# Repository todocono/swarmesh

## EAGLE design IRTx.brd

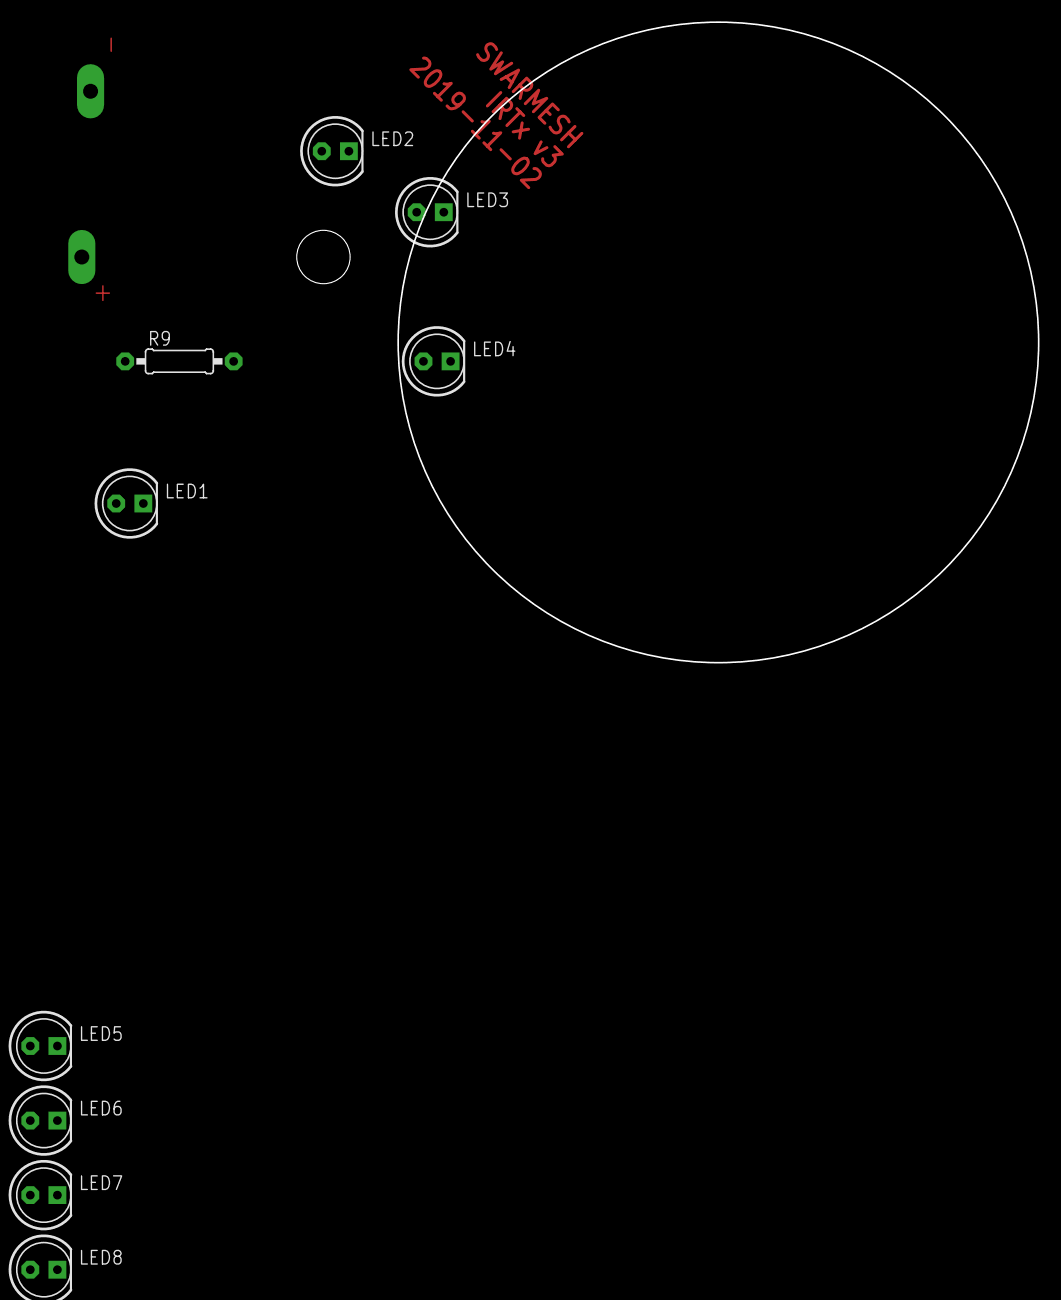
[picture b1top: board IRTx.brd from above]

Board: 2 copper layers, 60.0 x 60.0 mm, 11 parts (0 on the bottom side), 3 nets, no tracks yet.

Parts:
JP1: 3.3; 1X1-BIGPOGO
JP2: GND; 1X1-BIGPOGO
LED1, LED2, LED3, LED4, LED5, LED6, LED7, LED8: LED5MM
R9: 1k; 0207/10

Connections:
GND: JP2.P$1, LED1.K, LED2.K, LED3.K, LED4.K, LED5.K, LED6.K, LED7.K, LED8.K
unnamed: LED1.A, LED2.A, LED3.A, LED4.A, LED5.A, LED6.A, LED7.A, LED8.A, R9.1
VCC: JP1.P$1, R9.2

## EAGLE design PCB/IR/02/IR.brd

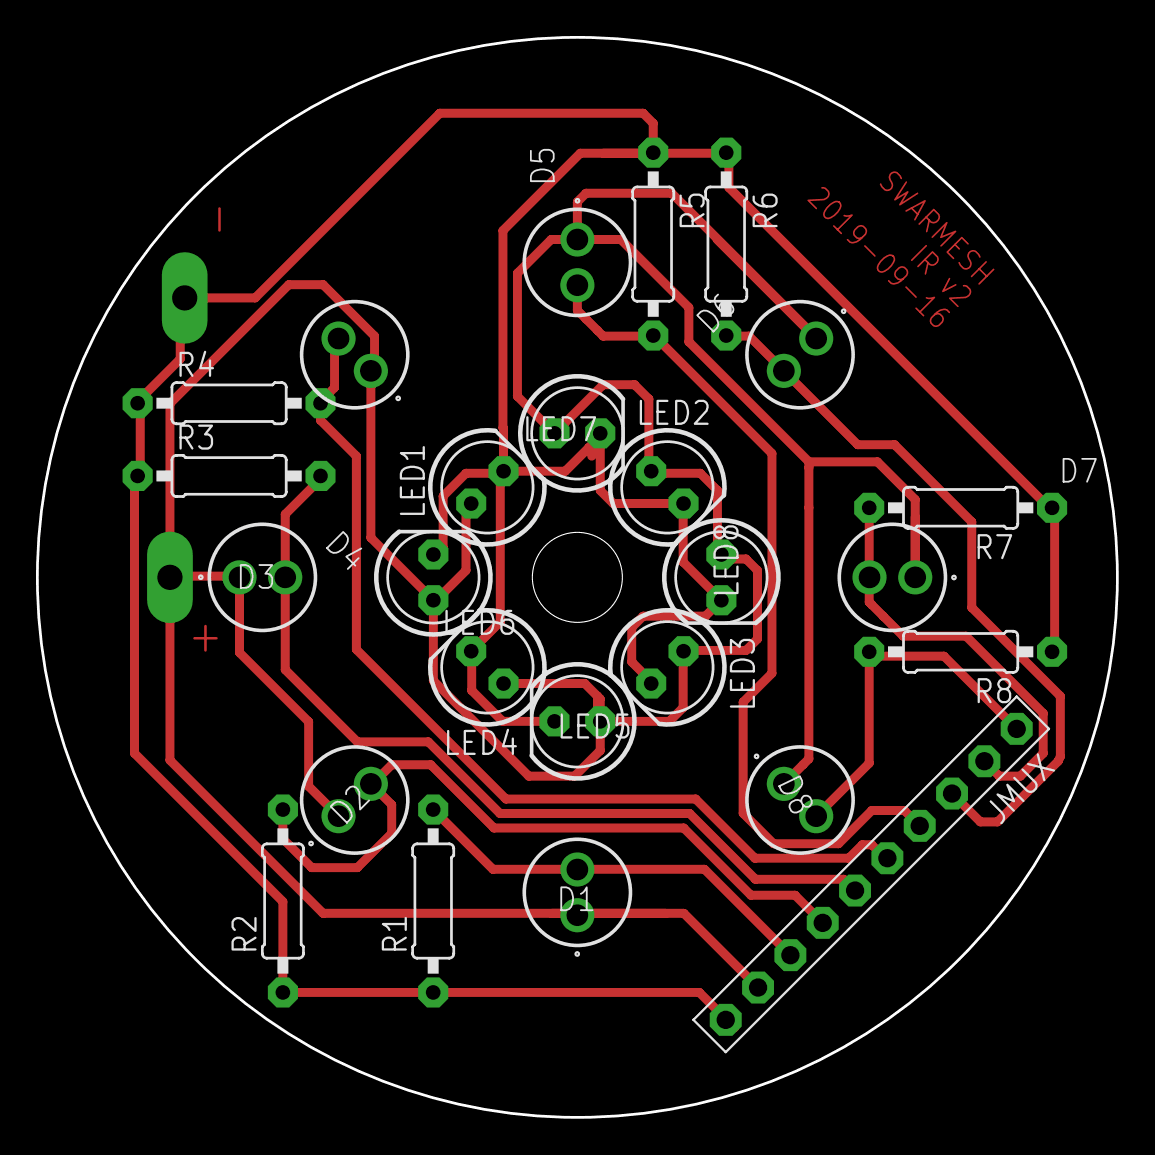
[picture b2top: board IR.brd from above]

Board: 2 copper layers, 60.0 x 60.0 mm, 27 parts (0 on the bottom side), 10 nets.

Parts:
D1, D2, D3, D4, D5, D6, D7, D8: SFH_203_PFA; SFH213_1
JMUX: PINHD-1X10; 1X10-BIG
JP9: GND; 1X1-BIGPOGO
JP10: 3.3; 1X1-BIGPOGO
LED1, LED2, LED3, LED4, LED5, LED6, LED7, LED8: LED5MM
R1, R2, R3, R4, R5, R6, R7, R8: 0207/10

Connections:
GND: JMUX.10, JP9.P$1, LED1.K, LED2.K, LED3.K, LED4.K, LED5.K, LED6.K, LED7.K, LED8.K, R1.1, R2.1, R3.1, R4.1, R5.1, R6.1, R7.1, R8.1
unnamed: D1.2, JMUX.8, R1.2
unnamed: D2.2, JMUX.7, R2.2
unnamed: D3.2, JMUX.6, R3.2
unnamed: D4.2, JMUX.5, R4.2
unnamed: D5.2, JMUX.4, R5.2
unnamed: D6.2, JMUX.3, R6.2
unnamed: D7.2, JMUX.2, R7.2
unnamed: D8.2, JMUX.1, R8.2
VCC: D1.1, D2.1, D3.1, D4.1, D5.1, D6.1, D7.1, D8.1, JMUX.9, JP10.P$1, LED1.A, LED2.A, LED3.A, LED4.A, LED5.A, LED6.A, LED7.A, LED8.A

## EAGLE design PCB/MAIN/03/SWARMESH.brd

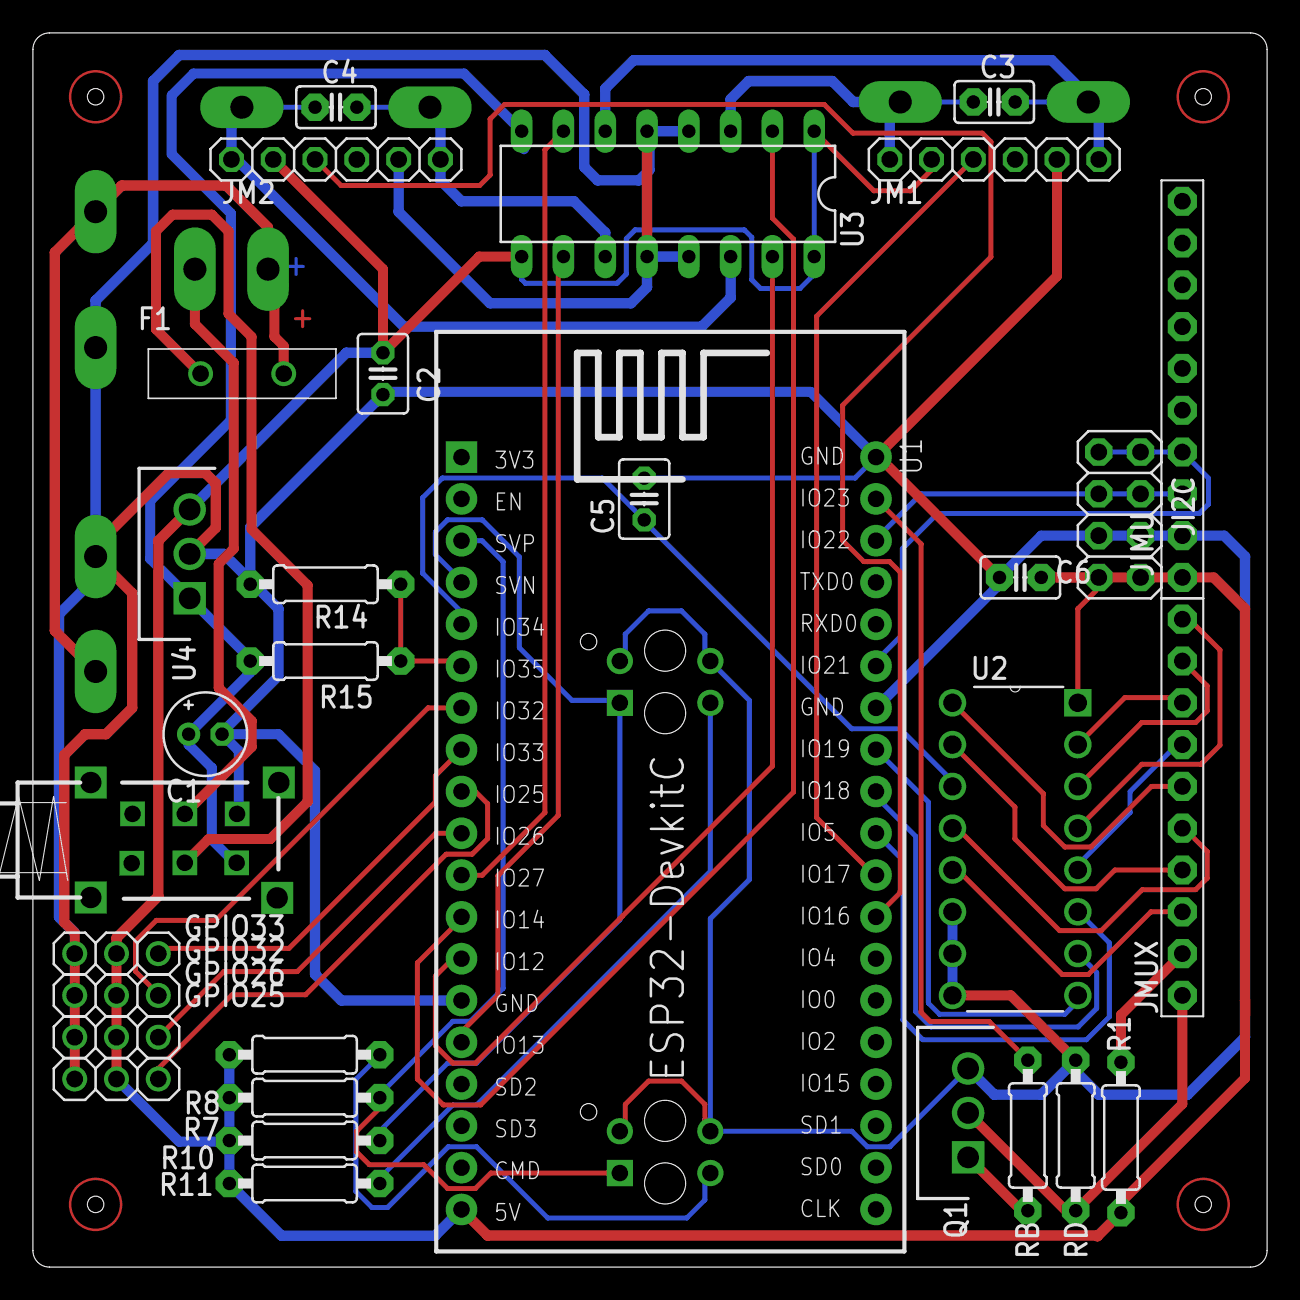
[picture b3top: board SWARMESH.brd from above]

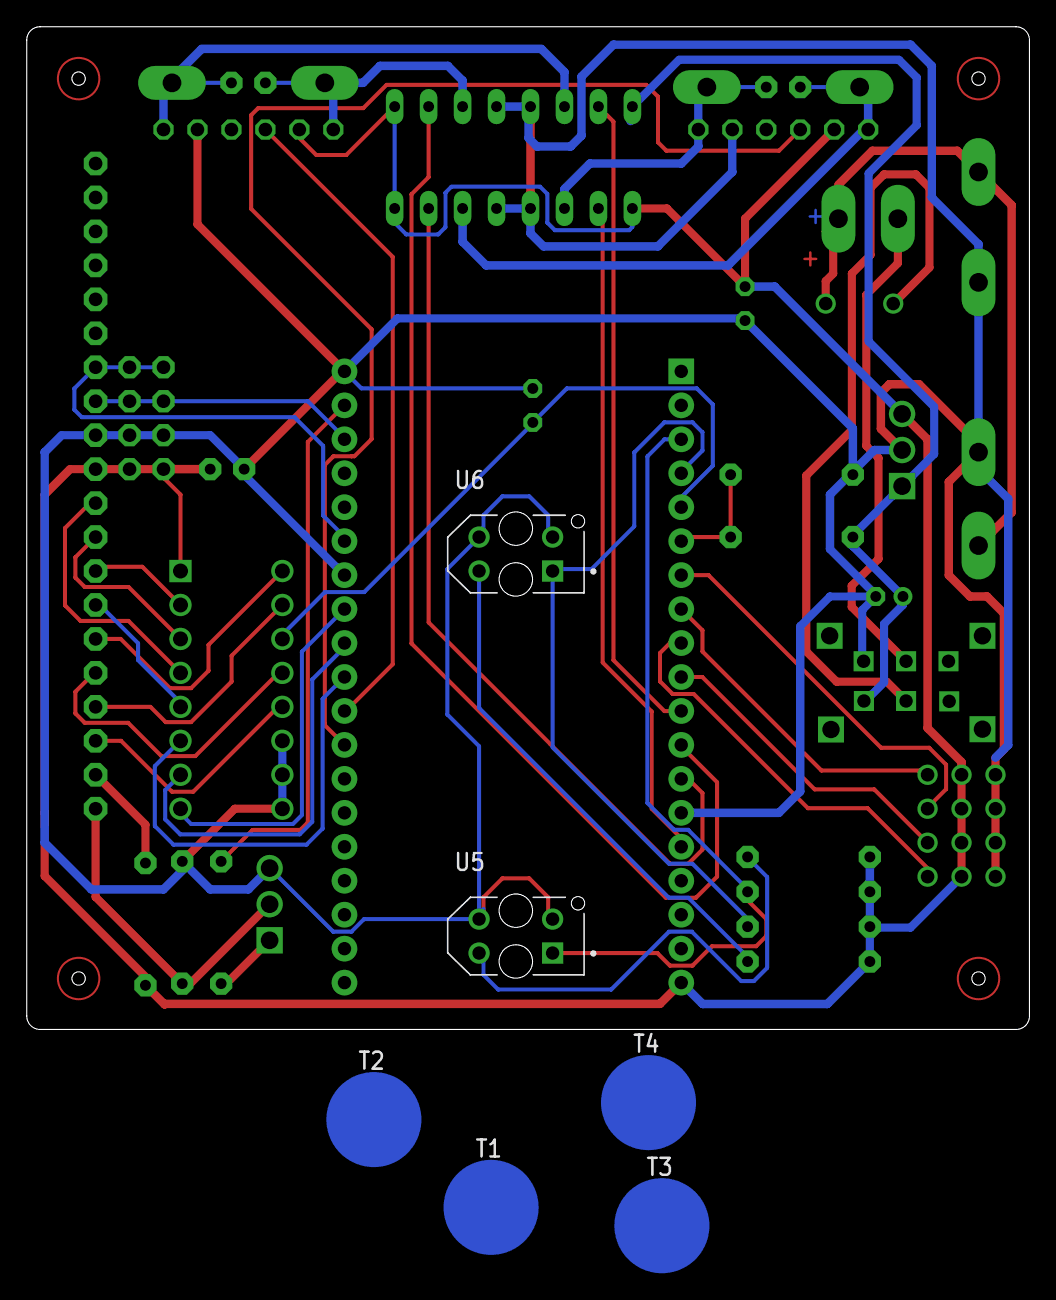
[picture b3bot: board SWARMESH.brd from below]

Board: 2 copper layers, 75.0 x 75.0 mm, 47 parts (7 on the bottom side), 47 nets.

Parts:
BAT+: 1X1-BIGPOGO
BAT-: 1X1-BIGPOGO
C1: 10uF; E2-5
C2, C5: C025-030X050
C3, C4, C6: C025-025X050
CHG1+, CHG1-, CHG2+, CHG2-: 1X1-BIGPOGO
F1: RUEF300K-2; RUEF300K2
GPIO25, GPIO26, GPIO32, GPIO33: 1X03
JI2C: 2X04
JIMU: PINHD-1X10; 1X10-BIG
JM1, JM2: 1X06
JMUX: PINHD-1X10; 1X10-BIG
JP1, JP2, JP3, JP4: 1X1-BIGPOGO
Q1: TIP122; TO270P460X1020X2008-3P
R1: 220; 0207/9
R7, R10: 1k; 0207/9
R8, R11: 100; 0207/9
R14: 10k; 0207/9
R15: 47k; 0207/9
RB: 1k; 0207/9
RD: 0; 0207/9
S1: PS22F03
T1, T2, T3, T4: SPRING-CONNECTOR
U1: ESP32DEVKITC; ESP32-DEVKITC
U2: CD4051BEE4; CD4051BEE4DIP
U3: L293D; DIL16
U4: L7805CV-DG; TO270P460X1020X2008-3P
U5, U6: TCRT5000L; XDCR_TCRT5000L

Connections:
ADCMX: C5.1, U1.5, U2.3
BATLVL: R14.2, R15.1, U1.6
E1A: JM1.3, U1.28
E2A: JM2.3, U1.27
GND: C1.-, C2.2, C5.2, C6.2, CHG1-.P$1, CHG2-.P$1, GPIO25.3, GPIO26.3, GPIO32.3, GPIO33.3, JI2C.3, JI2C.4, JIMU.2, JM1.5, JM2.5, Q1.3, R14.1, RD.2, S1.NO1, U1.14, U1.32, U1.38, U2.6, U2.7, U2.8, U3.4, U3.5, U3.12, U3.13, U4.2, U5.2, U5.3, U6.2, U6.3
IO5: U1.29, U2.11
IO12: U1.13, U3.15
IO13: U1.15, U3.10
IO14: U1.12, U3.2
IO25: GPIO25.1, U1.9
IO26: GPIO26.1, U1.10
IO27: U1.11, U3.7
IO32: GPIO32.1, U1.7
IO33: GPIO33.1, U1.8
IR1: R7.2, U1.3, U5.1
IR2: R10.2, U1.4, U6.1
IRTX: RB.2, U1.37
M1A: C3.1, JM1.1, JP1.P$1, U3.3
M1B: C3.2, JM1.6, JP2.P$1, U3.6
M2A: C4.1, JM2.1, JP4.P$1, U3.14
M2B: C4.2, JM2.6, JP3.P$1, U3.11
unnamed: Q1.1, RB.1
unnamed: F1.2, S1.C2
unnamed: BAT-.P$1, S1.C1
unnamed: JMUX.6, U2.4
unnamed: U1.30, U2.10
unnamed: U1.31, U2.9
unnamed: R11.1, U6.4
unnamed: R8.1, U5.4
unnamed: JMUX.5, U2.1
unnamed: JMUX.7, U2.2
unnamed: JMUX.8, U2.5
unnamed: BAT+.P$1, CHG1+.P$1, CHG2+.P$1, F1.1
unnamed: JMUX.9, R1.1
unnamed: JMUX.10, Q1.2, RD.1
unnamed: JMUX.1, U2.13
unnamed: JMUX.2, U2.14
unnamed: JMUX.4, U2.12
unnamed: JMUX.3, U2.15
SCL: JI2C.5, JI2C.6, JIMU.3, U1.36
SDA: JI2C.7, JI2C.8, JIMU.4, U1.33
TOUCH1: T1.P$2, U1.23
TOUCH2: T2.P$2, U1.24
TOUCH3: T3.P$2, U1.25
TOUCH4: T4.P$2, U1.26
V+: C1.+, R15.2, S1.NO2, U3.8, U4.1
VCC: C2.1, C6.1, GPIO25.2, GPIO26.2, GPIO32.2, GPIO33.2, JI2C.1, JI2C.2, JIMU.1, JM1.2, JM2.2, R1.2, R7.1, R8.2, R10.1, R11.2, U1.19, U2.16, U3.1, U3.9, U3.16, U4.3

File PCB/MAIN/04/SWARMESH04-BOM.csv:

"Part";"Value";"Device";"Package";"Description";"ALLIED_NUMBER";"ALLIED_PRICE-STOCK";"AVAILABILITY";"DESCRIPTION";"HEIGHT";"MANUFACTURER_NAME";"MANUFACTURER_PART_NUMBER";"MF";"MOUSER_PART_NUMBER";"MOUSER_PRICE-STOCK";"MP";"MPN";"OC_FARNELL";"OC_NEWARK";"PACKAGE";"PRICE";"RS_PART_NUMBER";"RS_PRICE-STOCK";"SF_ID";
"BAT+";"";"PINHD-1X1-BIGPOGO";"1X1-BIGPOGO";"Pin header 1x1 for 0.1" spacing";"";"";"";"";"";"";"";"";"";"";"";"";"";"";"";"";"";"";"";
"BAT-";"";"PINHD-1X1-BIGPOGO";"1X1-BIGPOGO";"Pin header 1x1 for 0.1" spacing";"";"";"";"";"";"";"";"";"";"";"";"";"";"";"";"";"";"";"";
"C1";"10uF";"CPOL-USE2-5";"E2-5";"POLARIZED CAPACITOR, American symbol";"";"";"";"";"";"";"";"";"";"";"";"";"";"";"";"";"";"";"";
"C2";"";"C-US025-030X050";"C025-030X050";"CAPACITOR, American symbol";"";"";"";"";"";"";"";"";"";"";"";"";"";"";"";"";"";"";"";
"C3";"";"C-US025-025X050";"C025-025X050";"CAPACITOR, American symbol";"";"";"";"";"";"";"";"";"";"";"";"";"";"";"";"";"";"";"";
"C4";"";"C-US025-025X050";"C025-025X050";"CAPACITOR, American symbol";"";"";"";"";"";"";"";"";"";"";"";"";"";"";"";"";"";"";"";
"C5";"";"C-US025-030X050";"C025-030X050";"CAPACITOR, American symbol";"";"";"";"";"";"";"";"";"";"";"";"";"";"";"";"";"";"";"";
"C6";"";"C-US025-025X050";"C025-025X050";"CAPACITOR, American symbol";"";"";"";"";"";"";"";"";"";"";"";"";"";"";"";"";"";"";"";
"CHG1+";"";"PINHD-1X1-BIGPOGO";"1X1-BIGPOGO";"Pin header 1x1 for 0.1" spacing";"";"";"";"";"";"";"";"";"";"";"";"";"";"";"";"";"";"";"";
"CHG1-";"";"PINHD-1X1-BIGPOGO";"1X1-BIGPOGO";"Pin header 1x1 for 0.1" spacing";"";"";"";"";"";"";"";"";"";"";"";"";"";"";"";"";"";"";"";
"CHG2+";"";"PINHD-1X1-BIGPOGO";"1X1-BIGPOGO";"Pin header 1x1 for 0.1" spacing";"";"";"";"";"";"";"";"";"";"";"";"";"";"";"";"";"";"";"";
"CHG2-";"";"PINHD-1X1-BIGPOGO";"1X1-BIGPOGO";"Pin header 1x1 for 0.1" spacing";"";"";"";"";"";"";"";"";"";"";"";"";"";"";"";"";"";"";"";
"F1";"RUEF300K-2";"RUEF300K-2";"RUEF300K2";"TE CONNECTIVITY / RAYCHEM - RUEF300K-2 - RESETTABLE FUSE, PTC, 30V, 3A, RADIAL";"";"";"";"TE CONNECTIVITY / RAYCHEM - RUEF300K-2 - RESETTABLE FUSE, PTC, 30V, 3A, RADIAL";"16.5mm";"TE CONNECTIVITY / RAYCHEM";"RUEF300K-2";"";"";"";"";"";"";"";"";"";"";"";"";
"GPIO25";"";"PINHD-1X3";"1X03";"PIN HEADER";"";"";"";"";"";"";"";"";"";"";"";"";"";"";"";"";"";"";"";
"GPIO26";"";"PINHD-1X3";"1X03";"PIN HEADER";"";"";"";"";"";"";"";"";"";"";"";"";"";"";"";"";"";"";"";
"GPIO32";"";"PINHD-1X3";"1X03";"PIN HEADER";"";"";"";"";"";"";"";"";"";"";"";"";"";"";"";"";"";"";"";
"GPIO33";"";"PINHD-1X3";"1X03";"PIN HEADER";"";"";"";"";"";"";"";"";"";"";"";"";"";"";"";"";"";"";"";
"JI2C";"";"PINHD-2X4";"2X04";"PIN HEADER";"";"";"";"";"";"";"";"";"";"";"";"";"";"";"";"";"";"";"";
"JIMU";"PINHD-1X10";"PINHD-1X10";"1X10-BIG";"Pin header 1x10 0.1" spacing";"";"";"";"";"";"";"";"";"";"";"";"";"";"";"";"";"";"";"";
"JM1";"";"PINHD-1X6";"1X06";"PIN HEADER";"";"";"";"";"";"";"";"";"";"";"";"";"";"";"";"";"";"";"";
"JM2";"";"PINHD-1X6";"1X06";"PIN HEADER";"";"";"";"";"";"";"";"";"";"";"";"";"";"";"";"";"";"";"";
"JMUX";"PINHD-1X10";"PINHD-1X10";"1X10-BIG";"Pin header 1x10 0.1" spacing";"";"";"";"";"";"";"";"";"";"";"";"";"";"";"";"";"";"";"";
"JP1";"";"PINHD-1X1-BIGPOGO";"1X1-BIGPOGO";"Pin header 1x1 for 0.1" spacing";"";"";"";"";"";"";"";"";"";"";"";"";"";"";"";"";"";"";"";
"JP2";"";"PINHD-1X1-BIGPOGO";"1X1-BIGPOGO";"Pin header 1x1 for 0.1" spacing";"";"";"";"";"";"";"";"";"";"";"";"";"";"";"";"";"";"";"";
"JP3";"";"PINHD-1X1-BIGPOGO";"1X1-BIGPOGO";"Pin header 1x1 for 0.1" spacing";"";"";"";"";"";"";"";"";"";"";"";"";"";"";"";"";"";"";"";
"JP4";"";"PINHD-1X1-BIGPOGO";"1X1-BIGPOGO";"Pin header 1x1 for 0.1" spacing";"";"";"";"";"";"";"";"";"";"";"";"";"";"";"";"";"";"";"";
"Q1";"TIP122";"TIP122";"TO270P460X1020X2008-3P";"TIP122, Darlington Transistor, NPN 8 A 100 V HFE:1000, 3-Pin, TO-220";"";"";"";"TIP122, Darlington Transistor, NPN 8 A 100 V HFE:1000, 3-Pin, TO-220";"4.6mm";"STMicroelectronics";"TIP122";"";"511-TIP122";"https://www.mouser.com/Search/Refine.aspx?Keyword=511-TIP122";"";"";"";"";"";"";"";"";"";
"R1";"220";"R-US_0207/9";"0207/9";"RESISTOR, American symbol";"";"";"";"";"";"";"";"";"";"";"";"";"";"";"";"";"";"";"";
"R7";"1k";"R-US_0207/9";"0207/9";"RESISTOR, American symbol";"";"";"";"";"";"";"";"";"";"";"";"";"";"";"";"";"";"";"";
"R8";"100";"R-US_0207/9";"0207/9";"RESISTOR, American symbol";"";"";"";"";"";"";"";"";"";"";"";"";"";"";"";"";"";"";"";
"R10";"1k";"R-US_0207/9";"0207/9";"RESISTOR, American symbol";"";"";"";"";"";"";"";"";"";"";"";"";"";"";"";"";"";"";"";
"R11";"100";"R-US_0207/9";"0207/9";"RESISTOR, American symbol";"";"";"";"";"";"";"";"";"";"";"";"";"";"";"";"";"";"";"";
"R14";"10k";"R-US_0207/9";"0207/9";"RESISTOR, American symbol";"";"";"";"";"";"";"";"";"";"";"";"";"";"";"";"";"";"";"";
"R15";"47k";"R-US_0207/9";"0207/9";"RESISTOR, American symbol";"";"";"";"";"";"";"";"";"";"";"";"";"";"";"";"";"";"";"";
"RB";"1k";"R-US_0207/9";"0207/9";"RESISTOR, American symbol";"";"";"";"";"";"";"";"";"";"";"";"";"";"";"";"";"";"";"";
"RD";"0";"R-US_0207/9";"0207/9";"RESISTOR, American symbol";"";"";"";"";"";"";"";"";"";"";"";"";"";"";"";"";"";"";"";
"S1";"";"SWITCH_320-938";"PS22F03";"TOGGLE SWITCH";"";"";"";"";"";"";"";"";"";"";"";"";"";"";"";"";"";"";"";
"T1";"";"CONN_01SPRING-CONN";"SPRING-CONNECTOR";"Single connection point. Often used as Generic Header-pin footprint for 0.1 inch spaced/style header connections";"";"";"";"";"";"";"";"";"";"";"";"";"";"";"";"";"";"";"PRT-11822";
"T2";"";"CONN_01SPRING-CONN";"SPRING-CONNECTOR";"Single connection point. Often used as Generic Header-pin footprint for 0.1 inch spaced/style header connections";"";"";"";"";"";"";"";"";"";"";"";"";"";"";"";"";"";"";"PRT-11822";
"T3";"";"CONN_01SPRING-CONN";"SPRING-CONNECTOR";"Single connection point. Often used as Generic Header-pin footprint for 0.1 inch spaced/style header connections";"";"";"";"";"";"";"";"";"";"";"";"";"";"";"";"";"";"";"PRT-11822";
"T4";"";"CONN_01SPRING-CONN";"SPRING-CONNECTOR";"Single connection point. Often used as Generic Header-pin footprint for 0.1 inch spaced/style header connections";"";"";"";"";"";"";"";"";"";"";"";"";"";"";"";"";"";"";"PRT-11822";
"U1";"ESP32DEVKITC";"ESP32DEVKITC";"ESP32-DEVKITC";"";"";"";"";"";"";"";"";"";"";"";"";"";"";"";"";"";"";"";"";
"U2";"CD4051BEE4";"CD4051BEE4";"CD4051BEE4DIP";"Multiplexer 8pin ADC/DAC";"";"";"";"";"";"";"";"";"";"";"";"";"";"";"";"";"";"";"";
"U3";"L293D";"L293D";"DIL16";"PUSH-PULL 4 CHANNEL DRIVER";"";"";"";"";"";"";"";"";"";"";"";"L293D";"9589619";"56P8249";"";"";"";"";"";
"U4";"L7805CV-DG";"L7805CV-DG";"TO270P460X1020X2008-3P";"Voltage Regulator 5V 4% 1.5A TO220 L7805CV-DG, Linear Voltage Regulator, Current Limit, Shut-Down 1.5A 5 V, 3-Pin TO220";"70390055";"http://www.alliedelec.com/stmicroelectronics-l7805cv-dg/70390055/";"";"Voltage Regulator 5V 4% 1.5A TO220 L7805CV-DG, Linear Voltage Regulator, Current Limit, Shut-Down 1.5A 5 V, 3-Pin TO220";"4.6mm";"STMicroelectronics";"L7805CV-DG";"";"511-L7805CV-DG";"https://www.mouser.com/Search/Refine.aspx?Keyword=511-L7805CV-DG";"";"";"";"";"";"";"7931346P";"http://uk.rs-online.com/web/p/products/7931346P";"";
"U5";"TCRT5000L";"TCRT5000L";"XDCR_TCRT5000L";"TCRT5000 Series 940 nm 100 mA 60 mA Transistor Output Reflective Optical Sensor";"";"";"Unavailable";" TCRT5000 Series 940 nm 100 mA 60 mA Transistor Output Reflective Optical Sensor ";"";"";"";"Vishay Semiconductor";"";"";"TCRT5000L";"";"";"";"PCB Mount Vishay";"None";"";"";"";
"U6";"TCRT5000L";"TCRT5000L";"XDCR_TCRT5000L";"TCRT5000 Series 940 nm 100 mA 60 mA Transistor Output Reflective Optical Sensor";"";"";"Unavailable";" TCRT5000 Series 940 nm 100 mA 60 mA Transistor Output Reflective Optical Sensor ";"";"";"";"Vishay Semiconductor";"";"";"TCRT5000L";"";"";"";"PCB Mount Vishay";"None";"";"";"";

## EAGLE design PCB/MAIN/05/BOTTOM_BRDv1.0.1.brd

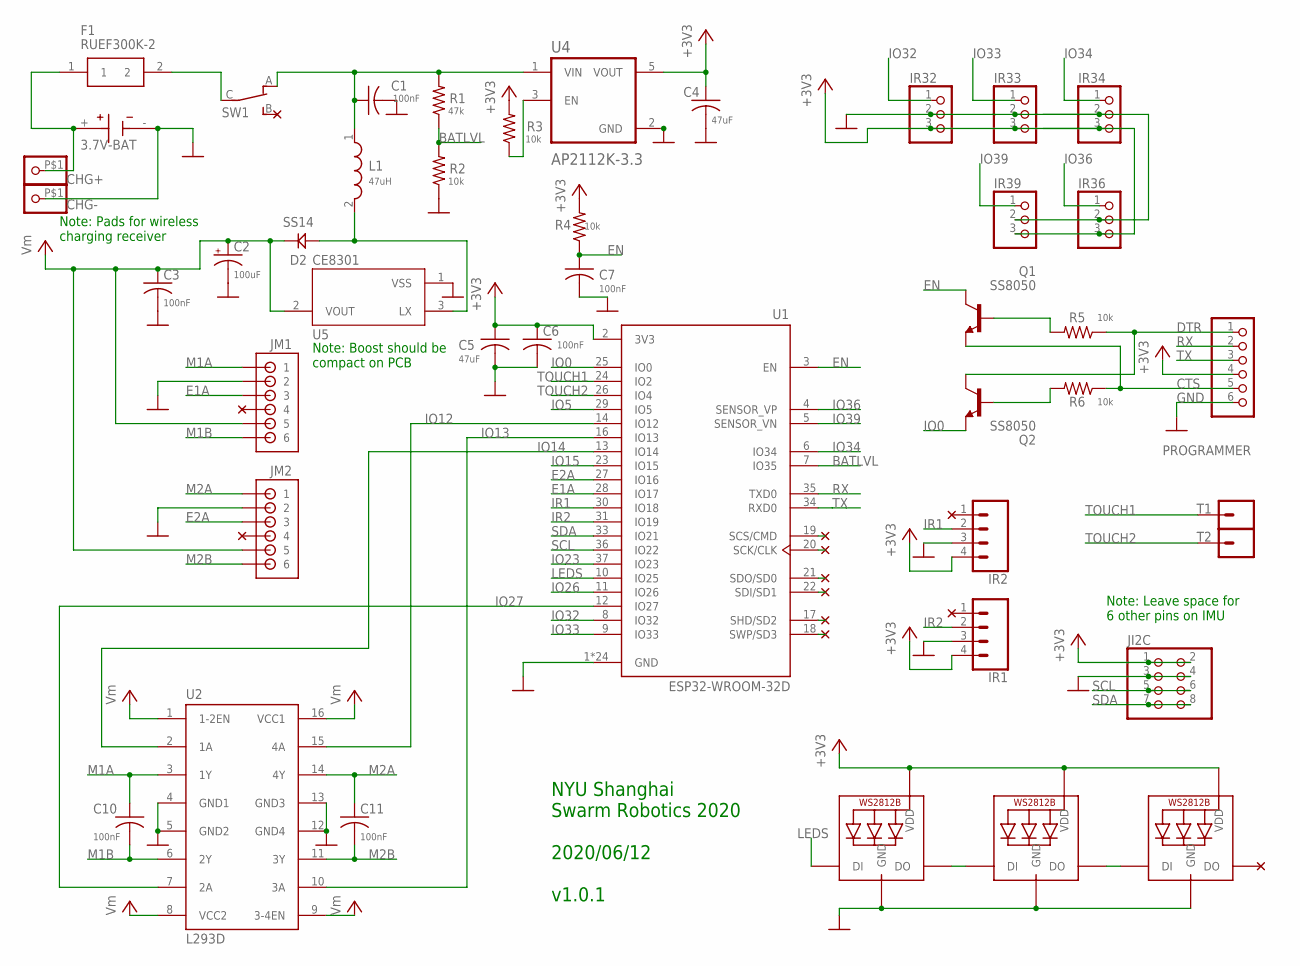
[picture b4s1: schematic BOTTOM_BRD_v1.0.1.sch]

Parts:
BT1: 3.7V-BAT; BAT_6S-AA
C1, C3, C6, C7, C10, C11: 100nF; C0805
C2: 100uF; 153CLV-0605
C4, C5: 47uF; C0805
CHARGING: WS2812B5050; WS2812B
CHG+: PINHD-1X1-BIGPOGO; 1X1-BIGPOGO
CHG-: PINHD-1X1-BIGPOGO; 1X1-BIGPOGO
D2: SS14; DO214
F1: RUEF300K-2; RUEF300K2
IR1, IR2: CONN_04; 1X04
IR32, IR33, IR34, IR36, IR39: PINHD-1X3; 1X03
JI2C: PINHD-2X4; 2X04
JM1, JM2: B6B-ZR
L1: 47uH; INDP5858X480N
POWER: WS2812B5050; WS2812B
PROGRAMMER: PINHD-1X6B; 1X06-BIG
Q1, Q2: SS8050; SOT23
R1: 47k; M0805
R2, R3, R4, R5, R6: 10k; M0805
STATE: WS2812B5050; WS2812B
SW1: CS12ANW03
T1, T2: CONN_01SPRING-CONN; SPRING-CONNECTOR
U1: ESP32-WROOM-32D; MODULE_ESP32-WROOM-32D
U2: L293D; DIL16
U4: AP2112K-3.3; SOT95P285X140-5N
U5: CE8301; REG_MCP1702T-3302E/MB

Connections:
+3V3: C4.1, C5.1, C6.1, CHARGING.1-VDD (VDD), IR1.4, IR2.4, IR32.3, IR33.3, IR34.3, IR36.3, IR39.3, JI2C.1, JI2C.2, POWER.1-VDD (VDD), PROGRAMMER.4, R3.2, R4.2, STATE.1-VDD (VDD), U1.2 (3V3), U4.5 (VOUT)
BATLVL: R1.1, R2.2, U1.7 (IO35)
CTS: PROGRAMMER.5, Q1.2 (E), R6.1
DTR: PROGRAMMER.1, Q2.3 (C), R5.1
E1A: JM1.3, U1.28 (IO17)
E2A: JM2.3, U1.27 (IO16)
EN: C7.1, Q1.3 (C), R4.1, U1.3 (EN)
GND: BT1.-, C1.2, C2.-, C3.2, C4.2, C5.2, C6.2, C7.2, CHARGING.3-GND (GND), CHG-.P$1, IR1.3, IR2.3, IR32.2, IR33.2, IR34.2, IR36.2, IR39.2, JI2C.3, JI2C.4, JM1.2, JM2.2, POWER.3-GND (GND), PROGRAMMER.6, R2.1, STATE.3-GND (GND), U1.1 (GND), U1.15 (GND), U1.38 (GND), U1.39_1 (GND), U1.39_2 (GND), U1.39_3 (GND), U1.39_4 (GND), U1.39_5 (GND), U1.39_6 (GND), U1.39_7 (GND), U1.39_8 (GND), U1.39_9 (GND), U1.39_10 (GND), U1.39_11 (GND), U1.39_12 (GND), U1.39_13 (GND), U1.39_14 (GND), U1.39_15 (GND), U1.39_16 (GND), U1.39_17 (GND), U1.39_18 (GND), U1.39_19 (GND), U1.39_20 (GND), U1.39_21 (GND), U2.4 (GND1), U2.5 (GND2), U2.12 (GND4), U2.13 (GND3), U4.2 (GND), U5.1 (VSS)
IO0: Q2.2 (E), U1.25 (IO0)
IO5: U1.29 (IO5)
IO12: U1.14 (IO12), U2.15 (4A)
IO13: U1.16 (IO13), U2.10 (3A)
IO14: U1.13 (IO14), U2.2 (1A)
IO15: U1.23 (IO15)
IO23: U1.37 (IO23)
IO26: U1.11 (IO26)
IO27: U1.12 (IO27), U2.7 (2A)
IO32: IR32.1, U1.8 (IO32)
IO33: IR33.1, U1.9 (IO33)
IO34: IR34.1, U1.6 (IO34)
IO36: IR36.1, U1.4 (SENSOR_VP)
IO39: IR39.1, U1.5 (SENSOR_VN)
IR1: IR2.2, U1.30 (IO18)
IR2: IR1.2, U1.31 (IO19)
LEDS: CHARGING.4-DIN (DI), U1.10 (IO25)
M1A: C10.1, JM1.1, U2.3 (1Y)
M1B: C10.2, JM1.6, U2.6 (2Y)
M2A: C11.1, JM2.1, U2.14 (4Y)
M2B: C11.2, JM2.6, U2.11 (3Y)
unnamed: BT1.+, CHG+.P$1, F1.1
unnamed: R3.1, U4.3 (EN)
unnamed: F1.2, SW1.C
unnamed: D2.ANODE, L1.2, U5.3 (LX)
unnamed: C1.1, L1.1, R1.2, SW1.A, U4.1 (VIN)
unnamed: CHARGING.2-DOUT (DO), POWER.4-DIN (DI)
unnamed: Q1.1 (B), R5.2
unnamed: POWER.2-DOUT (DO), STATE.4-DIN (DI)
unnamed: Q2.1 (B), R6.2
RX: PROGRAMMER.2, U1.35 (TXD0)
SCL: JI2C.5, JI2C.6, U1.36 (IO22)
SDA: JI2C.7, JI2C.8, U1.33 (IO21)
TOUCH1: T1.P$2, U1.24 (IO2)
TOUCH2: T2.P$2, U1.26 (IO4)
TX: PROGRAMMER.3, U1.34 (RXD0)
VCC: C2.+, C3.1, D2.CATHODE (KATHODE), JM1.5, JM2.5, U2.1 (1-2EN), U2.8 (VCC2), U2.9 (3-4EN), U2.16 (VCC1), U5.2 (VOUT)

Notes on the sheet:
NYU Shanghai Swarm Robotics 2020 2020/06/12 v1.0.1
Note: Pads for wireless charging receiver
Note: Boost should be compact on PCB
Note: Leave space for 6 other pins on IMU

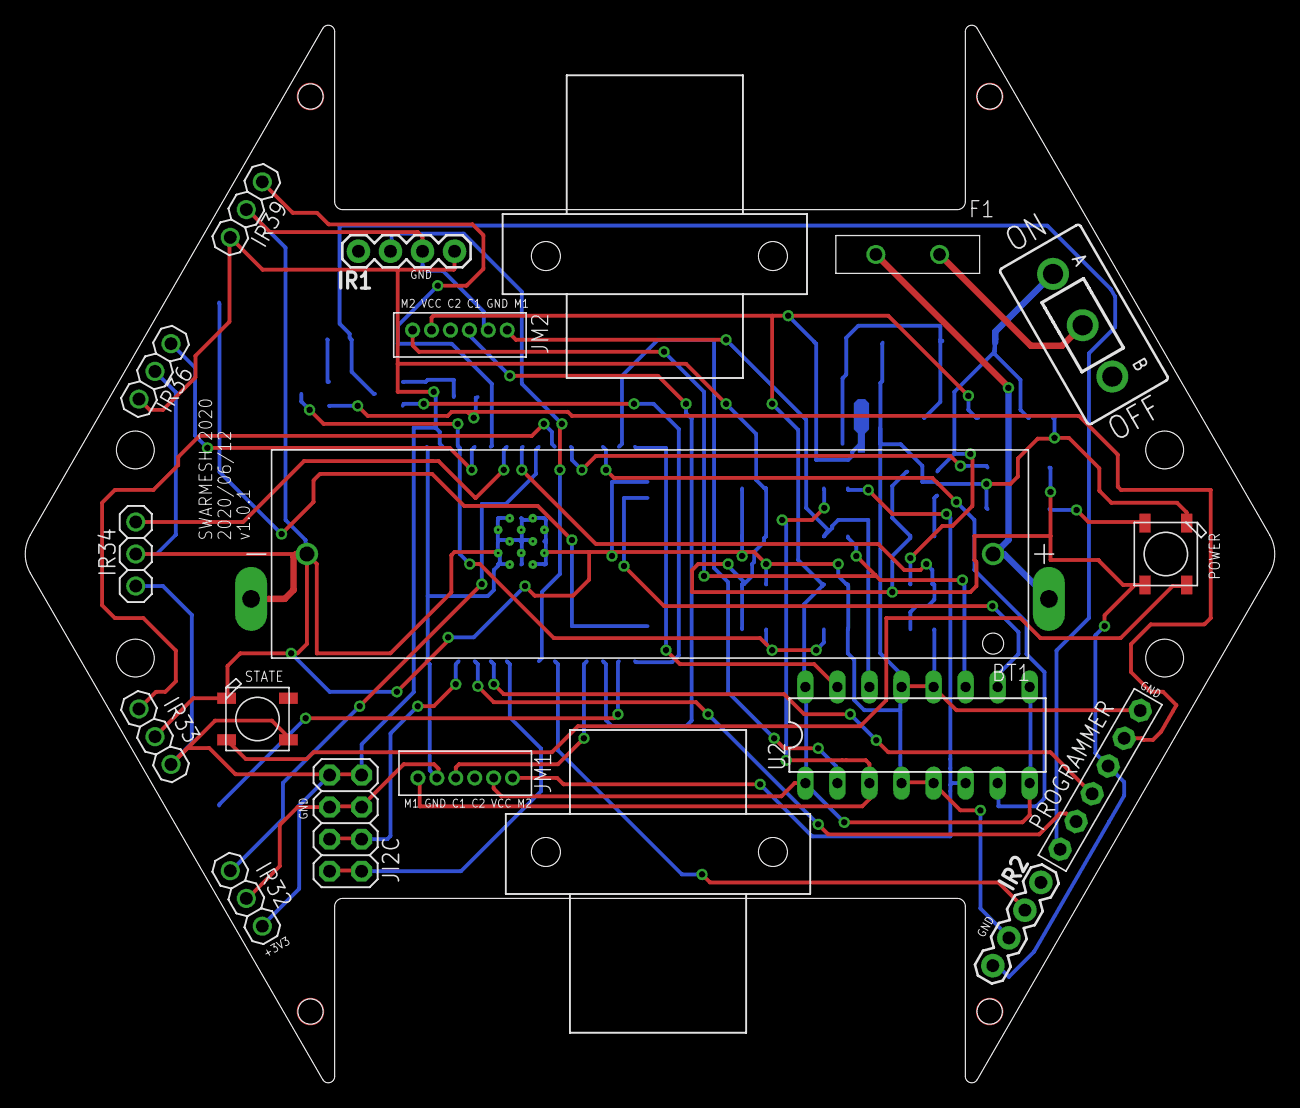
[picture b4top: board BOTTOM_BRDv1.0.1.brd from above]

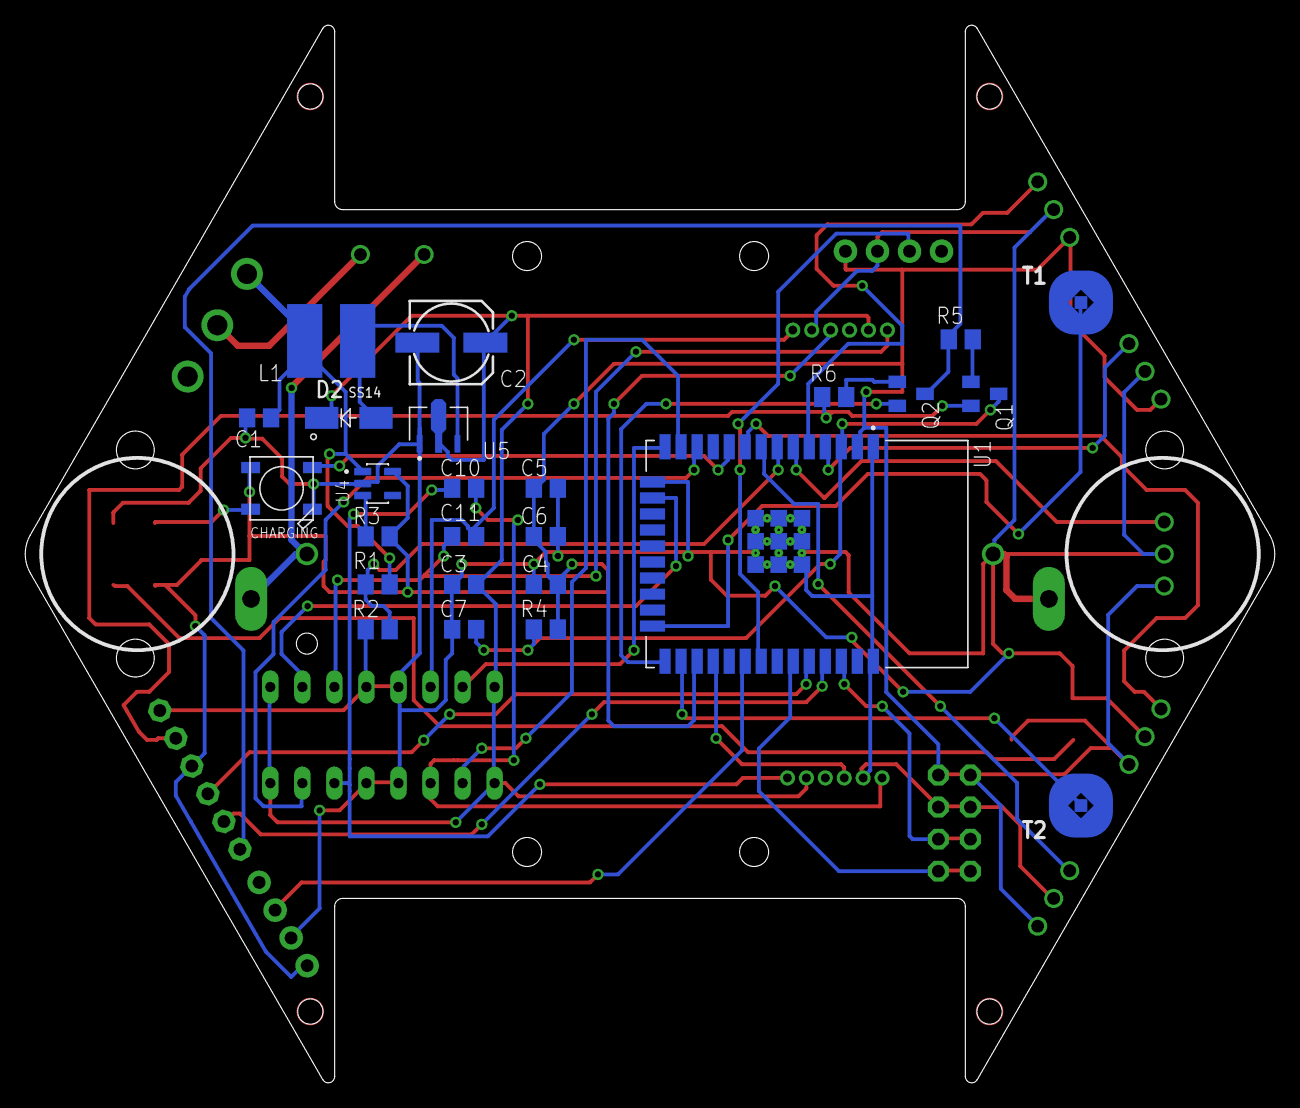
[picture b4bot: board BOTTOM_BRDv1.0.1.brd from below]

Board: 2 copper layers, 99.1 x 83.8 mm, 44 parts (26 on the bottom side), 41 nets.

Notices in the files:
PCB/MAIN/03/SWARMESH.brd:
Licensing: Creative Commons ShareAlike 4.0 International - https://creativecommons.org/licenses/by-sa/4.0
